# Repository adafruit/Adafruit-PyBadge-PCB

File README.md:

## Adafruit PyBadge PCB

<a href="http://www.adafruit.com/products/4200"><br/>
Click here to purchase one from the Adafruit shop</a>

PCB files for the Adafruit PyBadge. 

Format is EagleCAD schematic and board layout
* https://www.adafruit.com/product/4200

### Description

What's the size of a credit card and can run CircuitPython, MakeCode Arcade or Arduino? That's right, its the **Adafruit PyBadge!** We wanted to see how much we could cram into a ​3 3⁄8 × ​2 1⁄8 inch rounded rectangle, to make an all-in-one dev board with a lot of possibilities, and this is what we came up with.

The PyBadge is a compact board, like we said, it's credit card sized. It's powered by our favorite chip, the ATSAMD51, with 512KB of flash and 192KB of RAM. We add 2 MB of QSPI flash for file storage, handy for images, fonts, sounds, or game assets.

On the front you get a 1.8" 160x128 color TFT display with dimmable backlight - we have fast DMA support for drawing so updates are incredibly fast. There's also 8 silicone-top buttons, they are clicky but have a soft button top so they're nice and grippy. The buttons are arranged to mimic a gaming handheld, with a d-pad, 2 menu-select buttons and 2 fire-action buttons. There's also 5 NeoPixel LEDs to dazzle or track activity.

On the back we have a full Feather-compatible header socket set, so you can plug in any FeatherWing to expand the capabilities of the PyBadge. There's also 3 STEMMA connectors - two 3-pin with ADC/PWM capability and one 4-pin that connects to I2C - you can use this for Grove sensors as well.

For built in sensors, there's a light sensor that points out the front, and a 3-axis accelerometer that can detect taps and free-fall. To make bleeps and bloops, there's a built in buzzer-speaker. [For projects where you need more volume, you can plug in one of our 8 ohm speakers](https://www.adafruit.com/product/3923).

[You can power the PyBadge from any of our LiPoly batteries, but we like this 400mAh one](https://www.adafruit.com/product/3898.) An on-off switch will save battery power when not in use. Or power from the Micro USB port - it will also charge up the battery if one is attached.

Now, how to program it? Well you've got a lot of options!

[MakeCode Arcade is the easiest to start for making games](https://arcade.makecode.com/), you can drag-and-drop blocks and load games over the disk-drive bootloader
[CircuitPython](https://circuitpython.org/board/pybadge/) lets you draw graphics, play wave files and print out text in any fonts - all in Python! There's tons of sensor support as well.
Arduino is low level, powerful, but a little more challenging. [You can use Adafruit Arcada](https://github.com/adafruit/Adafruit_Arcada) to interface with the hardware and it will abstract some of the nitty-gritty details like reading buttons for you.
Here's a list of everything you get

 * **ATSAMD51J19** @ 120MHz with 3.3V logic/power - 512KB of FLASH + 192KB of RAM
 * **2 MB of SPI Flash** for storing images, sounds, animations, whatever!
 * **1.8" 160x128 Color TFT Display** connected to its own SPI port
 * **8 x Game/Control Buttons** with nice silicone button tops (these feel great)
 * **5 x NeoPixels** for badge dazzle, or game score-keeping
 * **Triple-axis accelerometer** (motion sensor)
 * **Light sensor**, reverse-mount so that it points out the front
 * **Built in buzzer mini-speaker**
 * **Mono Class-D speaker driver for** 4-8 ohm speakers, up to 2 Watts
 * LiPoly battery port with built in recharging capability
 * USB port for battery charging, programming and debugging
 * Two female header strips with Feather-compatible pinout so you can plug any FeatherWings in
 * JST ports for NeoPixels, sensor input, and I2C (you can fit I2C Grove connectors in here)
 * Reset button
 * On-Off switch

### License

Adafruit invests time and resources providing this open source design, please support Adafruit and open-source hardware by purchasing products from [Adafruit](https://www.adafruit.com)!

Designed by Limor Fried/Ladyada for Adafruit Industries.

Creative Commons Attribution/Share-Alike, all text above must be included in any redistribution. 
See license.txt for additional details.

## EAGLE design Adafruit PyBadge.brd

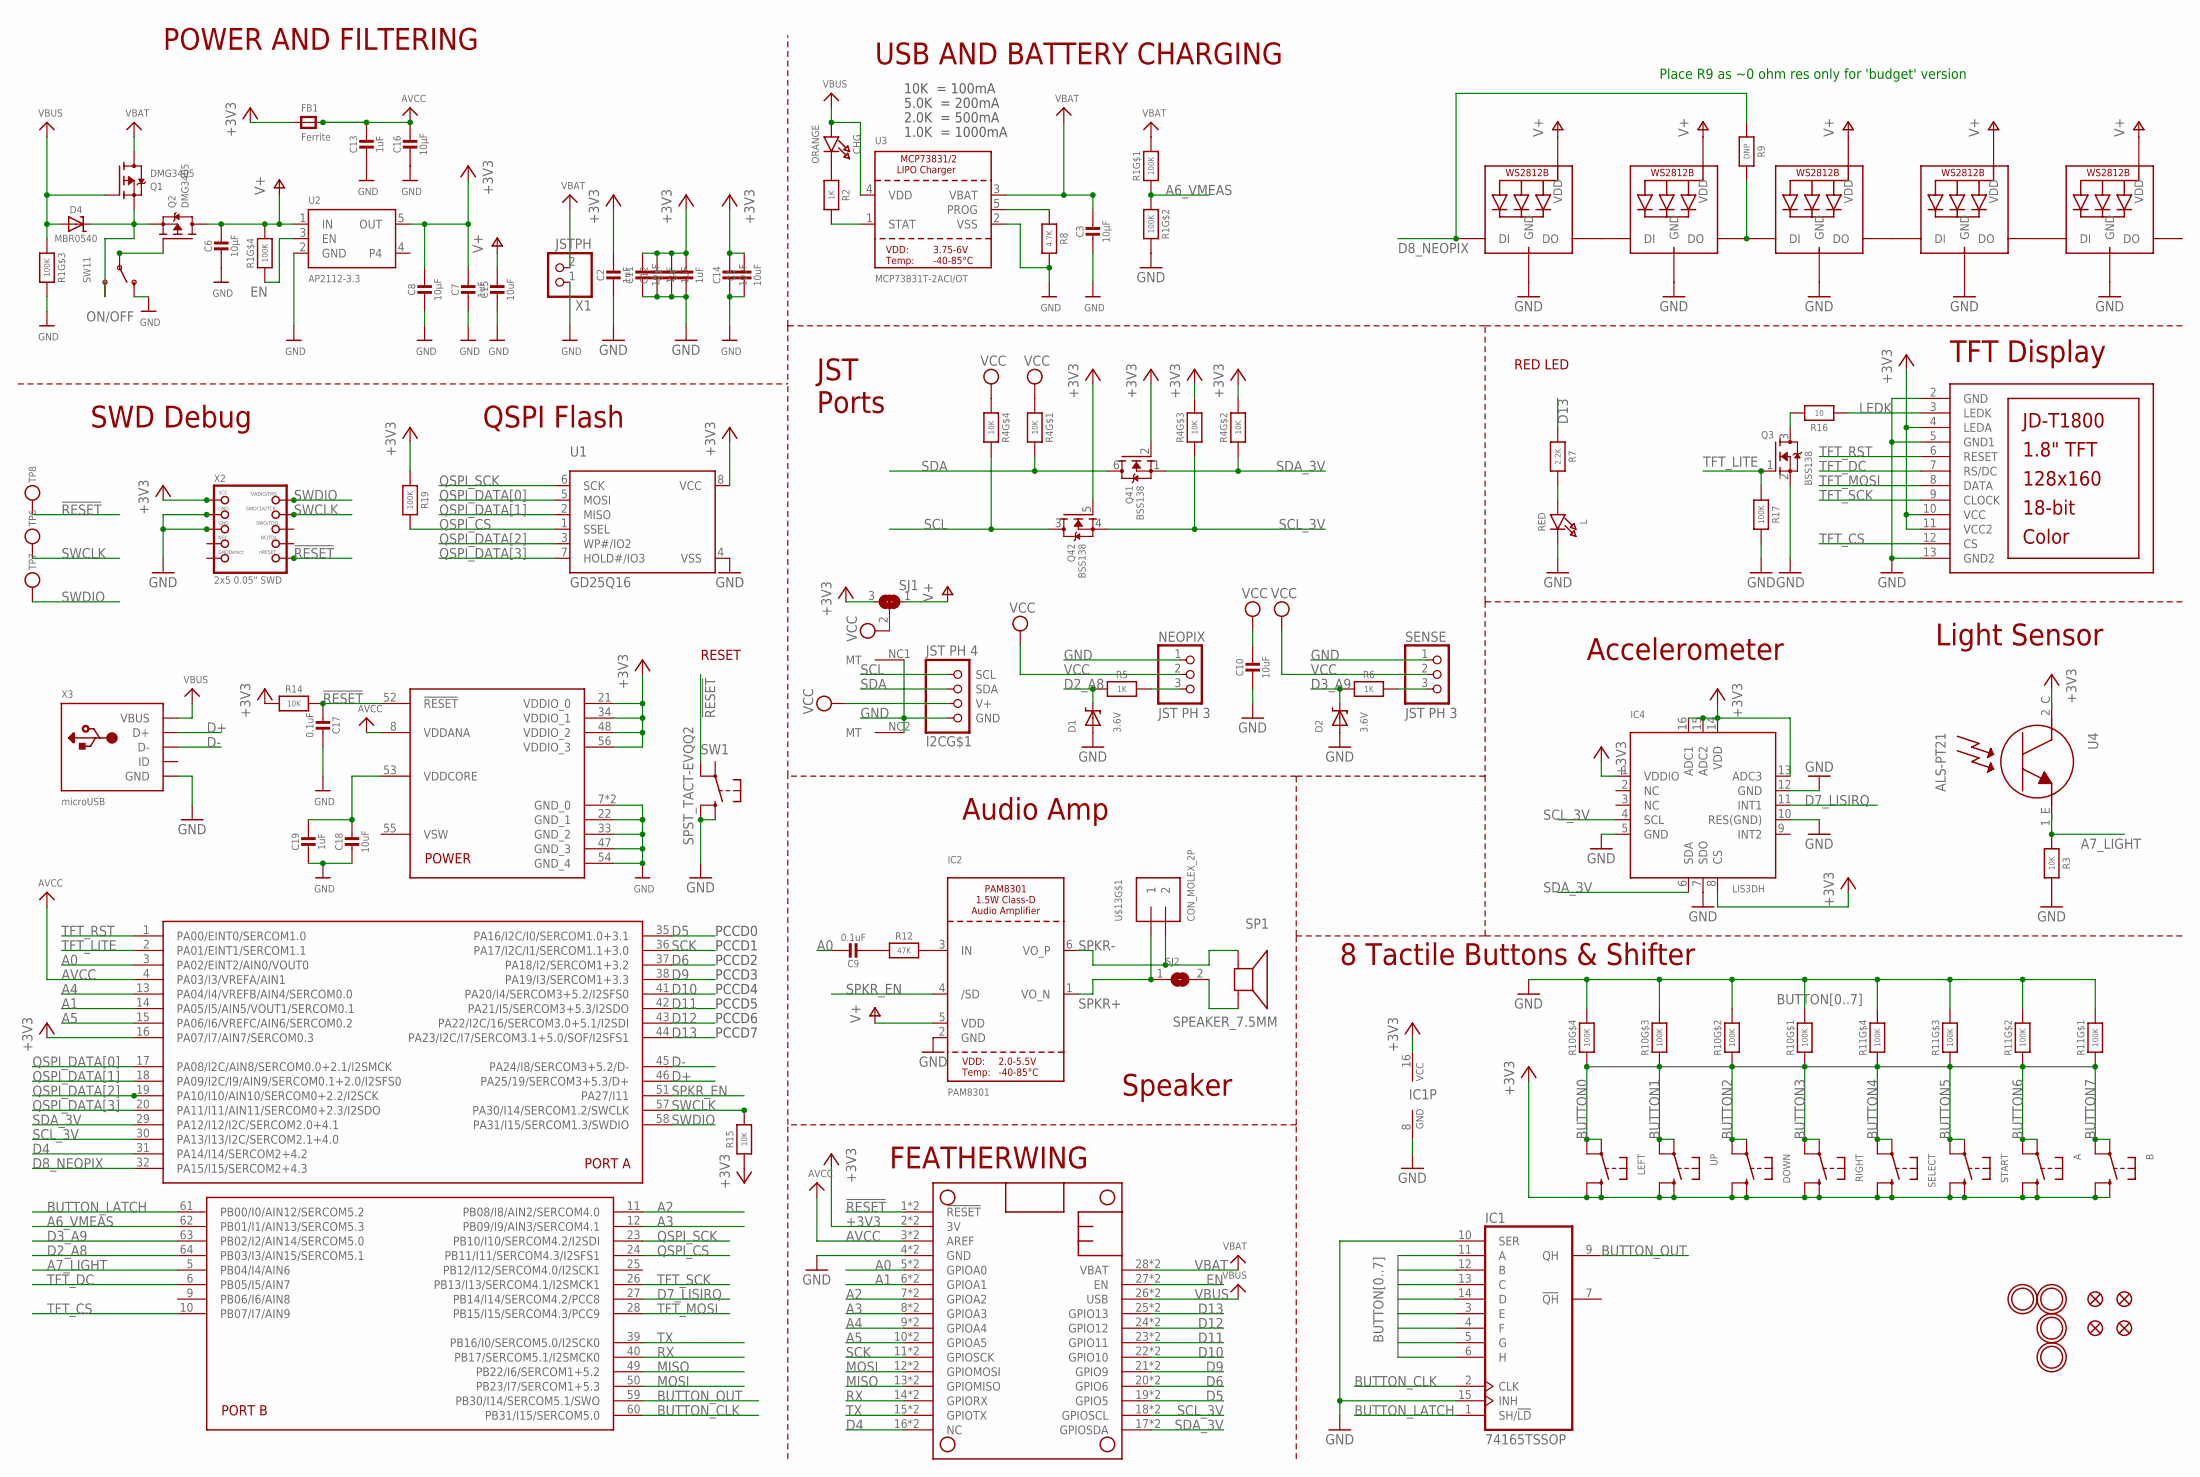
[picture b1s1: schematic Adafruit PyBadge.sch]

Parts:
A: SWITCH_TACT_SMT_6MMSMALL; 6MM_SMT
B: SWITCH_TACT_SMT_6MMSMALL; 6MM_SMT
C1, C2, C4, C7, C12, C13, C19: 1uF; 0603-NO
C3, C6, C8: 10µF; 0805-NO
C5, C10, C11, C14, C15, C18: 10uF; 0805-NO
C9, C17: 0.1uF; 0603-NO
C16: 10µF; _0805MP
CHG: ORANGE; CHIPLED_0805_NOOUTLINE
D1, D2: 3.6V; SOD-323
D4: MBR0540; SOD-123
DOWN: SWITCH_TACT_SMT_6MMSMALL; 6MM_SMT
FB1: Ferrite; 0805-NO
I2C: JST PH 4; JSTPH4
IC1: 74165TSSOP; TSSOP16
IC2: PAM8301; SOT23-6
IC4: LIS3DH; LGA16_3X3MM
L: RED; CHIPLED_0805_NOOUTLINE
LCD1: DISP_LCD_JDT1800; JD-T1800
LED1, LED2, LED3, LED4, LED5: WS2812B3535; LED3535
LEFT: SWITCH_TACT_SMT_6MMSMALL; 6MM_SMT
MS1: FEATHERWING_SMTDUALNOHOLES; FEATHERWING_SMT_NOHOLES
NEOPIX: JST PH 3; JSTPH3
Q1, Q2: DMG3405; SOT23-R
Q3: BSS138; SOT23-WIDE
Q4: BSS138; SOT363
R1, R10, R11: 100K; RESPACK_4X0603
R2, R5, R6: 1K; 0603-NO
R3, R14, R15: 10K; 0603-NO
R4: 10K; RESPACK_4X0603
R7: 2.2K; 0603-NO
R8: 4.7K; 0603-NO
R9: DNP; 0603-NO
R12: 47K; 0603-NO
R16: 10; 0603-NO
R17, R19: 100K; 0603-NO
RIGHT: SWITCH_TACT_SMT_6MMSMALL; 6MM_SMT
SELECT: SWITCH_TACT_SMT_6MMSMALL; 6MM_SMT
SENSE: JST PH 3; JSTPH3
SJ1: SOLDERJUMPER_2WAY; SOLDERJUMPER_2WAY_OPEN_NOPASTE
SJ2: SOLDERJUMPERCLOSED; SOLDERJUMPER_CLOSEDWIRE
SP1: SPEAKER_7.5MM; BUZZER_SMT_7.5MM
START: SWITCH_TACT_SMT_6MMSMALL; 6MM_SMT
SW1: SPST_TACT-EVQQ2; EVQ-Q2_SMALLER
SW11: SWITCH_SPDT; SPDT_SMT_SSSS811101
TP6, TP7, TP8: TESTPOINTROUND2MM; TESTPOINT_ROUND_2MM
U1: GD25Q16; SOIC8_208MIL
U2: AP2112-3.3; SOT23-5
U3: MCP73831T-2ACI/OT; SOT23-5
U4: ALS-PT21; ALS-PT26-21C
U$5, U$6, U$15, U$17: MOUNTINGHOLE3.0THIN; MOUNTINGHOLE_3.0_PLATEDTHIN
U$13: CON_MOLEX_2P; 53398-0271
U$24: ATSAMD51J19; PQFN64-1
U$34, U$35, U$42, U$43: FIDUCIAL_1MM
UP: SWITCH_TACT_SMT_6MMSMALL; 6MM_SMT
X1: JSTPH; JSTPH2
X2: 2x5 0.05" SWD; 2X05_1.27MM_BOX_POSTS
X3: microUSB; 4UCONN_20329_V2

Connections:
!RESET: C17.2, MS1.1 (!RESET), MS1.1B (!RESET), R14.2, SW1.A' (P1), TP8.P$1, U$24.52 (!RESET), X2.10 (NRESET)
+3V3: A.B (S), A.B' (S1), B.B (S), B.B' (S1), C1.1, C2.1, C4.1, C5.1, C7.1, C8.1, C11.1, C12.1, C14.1, DOWN.B (S), DOWN.B' (S1), FB1.1, IC1.16 (VCC), IC4.1 (VDDIO), IC4.8 (CS), IC4.13 (ADC3), IC4.14 (VDD), IC4.15 (ADC2), IC4.16 (ADC1), LCD1.4 (LEDA), LCD1.10 (VCC), LCD1.11 (VCC2), LEFT.B (S), LEFT.B' (S1), MS1.2 (3V), MS1.2B (3V), Q4.2 (G), Q4.5 (G), R4.2 (1), R4.3 (1), R14.1, R15.1, R19.1, RIGHT.B (S), RIGHT.B' (S1), SELECT.B (S), SELECT.B' (S1), SJ1.3, START.B (S), START.B' (S1), U1.8 (VCC), U2.5 (OUT), U4.2_C (C), U$24.16 (PA07/I7/AIN7/SERCOM0.3), U$24.21 (VDDIO_0), U$24.34 (VDDIO_1), U$24.48 (VDDIO_2), U$24.56 (VDDIO_3), UP.B (S), UP.B' (S1), X2.1 (VCC)
A0: C9.1, MS1.5 (GPIOA0), MS1.5B (GPIOA0), U$24.3 (PA02/EINT2/AIN0/VOUT0)
A1: MS1.6 (GPIOA1), MS1.6B (GPIOA1), U$24.14 (PA05/I5/AIN5/VOUT1/SERCOM0.1)
A2: MS1.7 (GPIOA2), MS1.7B (GPIOA2), U$24.11 (PB08/I8/AIN2/SERCOM4.0)
A3: MS1.8 (GPIOA3), MS1.8B (GPIOA3), U$24.12 (PB09/I9/AIN3/SERCOM4.1)
A4: MS1.9 (GPIOA4), MS1.9B (GPIOA4), U$24.13 (PA04/I4/VREFB/AIN4/SERCOM0.0)
A5: MS1.10 (GPIOA5), MS1.10B (GPIOA5), U$24.15 (PA06/I6/VREFC/AIN6/SERCOM0.2)
A6_VMEAS: R1.1, R1.2 (1), U$24.62 (PB01/I1/AIN13/SERCOM5.3)
A7_LIGHT: R3.2, U4.1_E (E), U$24.5 (PB04/I4/AIN6)
AVCC: C13.1, C16.1, FB1.2, MS1.3 (AREF), MS1.3B (AREF), U$24.4 (PA03/I3/VREFA/AIN1), U$24.8 (VDDANA)
BUTTON0: IC1.11 (A), LEFT.A, LEFT.A' (P1), R10.4 (1)
BUTTON1: IC1.12 (B), R10.3 (1), UP.A, UP.A' (P1)
BUTTON2: DOWN.A, DOWN.A' (P1), IC1.13 (C), R10.2 (1)
BUTTON3: IC1.14 (D), R10.1, RIGHT.A, RIGHT.A' (P1)
BUTTON4: IC1.3 (E), R11.4 (1), SELECT.A, SELECT.A' (P1)
BUTTON5: IC1.4 (F), R11.3 (1), START.A, START.A' (P1)
BUTTON6: A.A, A.A' (P1), IC1.5 (G), R11.2 (1)
BUTTON7: B.A, B.A' (P1), IC1.6 (H), R11.1
BUTTON_CLK: IC1.2 (CLK), U$24.60 (PB31/I15/SERCOM5.0)
BUTTON_LATCH: IC1.1 (SH/!LD), U$24.61 (PB00/I0/AIN12/SERCOM5.2)
BUTTON_OUT: IC1.9 (QH), U$24.59 (PB30/I14/SERCOM5.1/SWO)
CHG_LED: R2.2, U3.1 (STAT)
CHG_RATE: R8.1, U3.5 (PROG)
D2_: NEOPIX.3, R5.1
D2_A8: D1.C, R5.2, U$24.64 (PB03/I3/AIN15/SERCOM5.1)
D3_: R6.1, SENSE.3
D3_A9: D2.C, R6.2, U$24.63 (PB02/I2/AIN14/SERCOM5.0)
D4: MS1.16 (NC), MS1.16B (NC), U$24.31 (PA14/I14/SERCOM2+4.2)
D5: MS1.19 (GPIO5), MS1.19B (GPIO5), U$24.35 (PA16/I2C/I0/SERCOM1.0+3.1)
D6: MS1.20 (GPIO6), MS1.20B (GPIO6), U$24.37 (PA18/I2/SERCOM1+3.2)
D7_LISIRQ: IC4.11 (INT1), U$24.27 (PB14/I14/SERCOM4.2/PCC8)
D8_NEOPIX: LED1.1 (DI), R9.1, U$24.32 (PA15/I15/SERCOM2+4.3)
D9: MS1.21 (GPIO9), MS1.21B (GPIO9), U$24.38 (PA19/I3/SERCOM1+3.3)
D10: MS1.22 (GPIO10), MS1.22B (GPIO10), U$24.41 (PA20/I4/SERCOM3+5.2/I2SFS0)
D11: MS1.23 (GPIO11), MS1.23B (GPIO11), U$24.42 (PA21/I5/SERCOM3+5.3/I2SDO)
D12: MS1.24 (GPIO12), MS1.24B (GPIO12), U$24.43 (PA22/I2C/16/SERCOM3.0+5.1/I2SDI)
D13: MS1.25 (GPIO13), MS1.25B (GPIO13), R7.1, U$24.44 (PA23/I2C/I7/SERCOM3.1+5.0/SOF/I2SFS1)
D+: U$24.46 (PA25/19/SERCOM3+5.3/D+), X3.D+
D-: U$24.45 (PA24/I8/SERCOM3+5.2/D-), X3.D-
EN: MS1.27 (EN), MS1.27B (EN), R1.4 (1), U2.3 (EN)
GND: C1.2, C2.2, C3.2, C4.2, C5.2, C6.2, C7.2, C8.2, C10.2, C11.2, C12.2, C13.2, C14.2, C15.2, C16.2, C17.1, C18.2, C19.2, D1.A, D2.A, I2C.1 (GND), I2C.NC1 (MT), I2C.NC2 (MT), IC1.8 (GND), IC1.10 (SER), IC1.15 (INH), IC2.2 (GND), IC4.5 (GND), IC4.7 (SDO), IC4.10 (RES(GND)), IC4.12 (GND), L.C, LCD1.2 (GND), LCD1.5 (GND1), LCD1.13 (GND2), LED1.4 (GND), LED2.4 (GND), LED3.4 (GND), LED4.4 (GND), LED5.4 (GND), MS1.4 (GND), MS1.4B (GND), NEOPIX.1, Q3.2 (S), R1.6 (2), R1.7 (2), R3.1, R8.2, R10.5 (2), R10.6 (2), R10.7 (2), R10.8 (2), R11.5 (2), R11.6 (2), R11.7 (2), R11.8 (2), R17.2, SENSE.1, SW1.B (S), SW1.B' (S1), SW11.A (O), U1.4 (VSS), U2.2 (GND), U3.2 (VSS), U$24.7 (GND_0), U$24.22 (GND_1), U$24.33 (GND_2), U$24.47 (GND_3), U$24.54 (GND_4), U$24.EXP (GND_0), X1.1, X2.3 (GND), X2.5 (GND), X3.BASE@1 (GND), X3.BASE@2 (GND), X3.GND, X3.SPRT@1 (GND), X3.SPRT@2 (GND), X3.SPRT@3 (GND), X3.SPRT@4 (GND)
LEDK: LCD1.3 (LEDK), R16.1
MISO: MS1.13 (GPIOMISO), MS1.13B (GPIOMISO), U$24.49 (PB22/I6/SERCOM1+5.2)
MOSI: MS1.12 (GPIOMOSI), MS1.12B (GPIOMOSI), U$24.50 (PB23/I7/SERCOM1+5.3)
unnamed: CHG.C, R2.1
unnamed: L.A, R7.2
unnamed: LED1.3 (DO), LED2.1 (DI)
unnamed: LED2.3 (DO), LED3.1 (DI), R9.2
unnamed: LED3.3 (DO), LED4.1 (DI)
unnamed: Q3.3 (D), R16.2
unnamed: LED4.3 (DO), LED5.1 (DI)
unnamed: D4.C, Q1.2 (S), Q2.2 (S), SW11.C (S)
unnamed: C9.2, R12.1
unnamed: IC2.3 (IN), R12.2
unnamed: SJ2.2, SP1.-
ON/OFF: Q2.1 (G), SW11.B
QSPI_CS: R19.2, U1.1 (SSEL), U$24.24 (PB11/I11/SERCOM4.3/I2SFS1)
QSPI_DATA[0]: U1.5 (MOSI), U$24.17 (PA08/I2C/AIN8/SERCOM0.0+2.1/I2SMCK)
QSPI_DATA[1]: U1.2 (MISO), U$24.18 (PA09/I2C/I9/AIN9/SERCOM0.1+2.0/I2SFS0)
QSPI_DATA[2]: U1.3 (WP#/IO2), U$24.19 (PA10/I10/AIN10/SERCOM0+2.2/I2SCK)
QSPI_DATA[3]: U1.7 (HOLD#/IO3), U$24.20 (PA11/I11/AIN11/SERCOM0+2.3/I2SDO)
QSPI_SCK: U1.6 (SCK), U$24.23 (PB10/I10/SERCOM4.2/I2SDI)
RX: MS1.14 (GPIORX), MS1.14B (GPIORX), U$24.40 (PB17/SERCOM5.1/I2SMCK0)
SCK: MS1.11 (GPIOSCK), MS1.11B (GPIOSCK), U$24.36 (PA17/I2C/I1/SERCOM1.1+3.0)
SCL: I2C.4 (SCL), Q4.3 (D), R4.5 (2)
SCL_3V: IC4.4 (SCL), MS1.18 (GPIOSCL), MS1.18B (GPIOSCL), Q4.4 (S), R4.6 (2), U$24.30 (PA13/I13/I2C/SERCOM2.1+4.0)
SDA: I2C.3 (SDA), Q4.6 (D), R4.8 (2)
SDA_3V: IC4.6 (SDA), MS1.17 (GPIOSDA), MS1.17B (GPIOSDA), Q4.1 (S), R4.7 (2), U$24.29 (PA12/I12/I2C/SERCOM2.0+4.1)
SPKR+: IC2.1 (VO_N), SJ2.1, U$13.1
SPKR-: IC2.6 (VO_P), SP1.+, U$13.2
SPKR_EN: IC2.4 (/SD), U$24.51 (PA27/I11)
SWCLK: R15.2, TP6.P$1, U$24.57 (PA30/I14/SERCOM1.2/SWCLK), X2.4 (SWDCLK)
SWDIO: TP7.P$1, U$24.58 (PA31/I15/SERCOM1.3/SWDIO), X2.2 (SWDIO)
TFT_CS: LCD1.12 (CS), U$24.10 (PB07/I7/AIN9)
TFT_DC: LCD1.7 (RS/DC), U$24.6 (PB05/I5/AIN7)
TFT_LITE: Q3.1 (G), R17.1, U$24.2 (PA01/EINT1/SERCOM1.1)
TFT_MOSI: LCD1.8 (DATA), U$24.28 (PB15/I15/SERCOM4.3/PCC9)
TFT_RST: LCD1.6 (RESET), U$24.1 (PA00/EINT0/SERCOM1.0)
TFT_SCK: LCD1.9 (CLOCK), U$24.26 (PB13/I13/SERCOM4.1/I2SMCK1)
TX: MS1.15 (GPIOTX), MS1.15B (GPIOTX), U$24.39 (PB16/I0/SERCOM5.0/I2SCK0)
V+: C6.1, C15.1, IC2.5 (VDD), LED1.2 (VDD), LED2.2 (VDD), LED3.2 (VDD), LED4.2 (VDD), LED5.2 (VDD), Q2.3 (D), R1.5 (2), SJ1.1, U2.1 (IN)
VBAT: C3.1, MS1.28 (VBAT), MS1.28B (VBAT), Q1.3 (D), R1.8 (2), U3.3 (VBAT), X1.2
VBUS: CHG.A, D4.A, MS1.26 (USB), MS1.26B (USB), Q1.1 (G), R1.3 (1), U3.4 (VDD), X3.VBUS
VCC: C10.1, I2C.2 (V+), NEOPIX.2, R4.1, R4.4 (1), SENSE.2, SJ1.2
VDDCORE2: C18.1, C19.1, U$24.53 (VDDCORE)

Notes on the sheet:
POWER AND FILTERING
RESET
10K = 100mA
5.0K = 200mA
2.0K = 500mA
1.0K = 1000mA
USB AND BATTERY CHARGING
RED LED
Accelerometer
Light Sensor
FEATHERWING
TFT Display
Audio Amp
JST Ports
PCCD0
PCCD1
PCCD2
PCCD3
PCCD4
PCCD5
PCCD6
PCCD7
Speaker
Place R9 as ~0 ohm res only for 'budget' version
8 Tactile Buttons & Shifter
SWD Debug
QSPI Flash

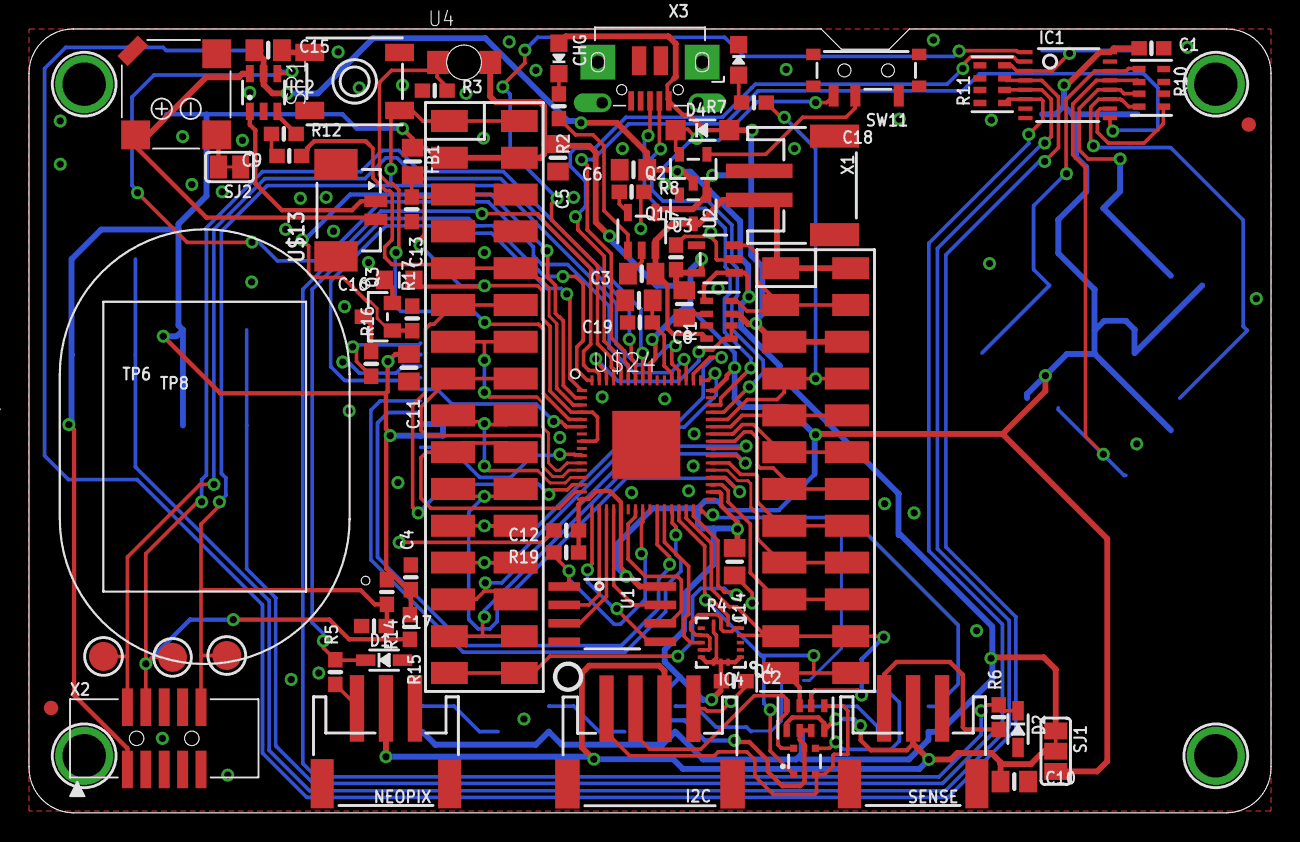
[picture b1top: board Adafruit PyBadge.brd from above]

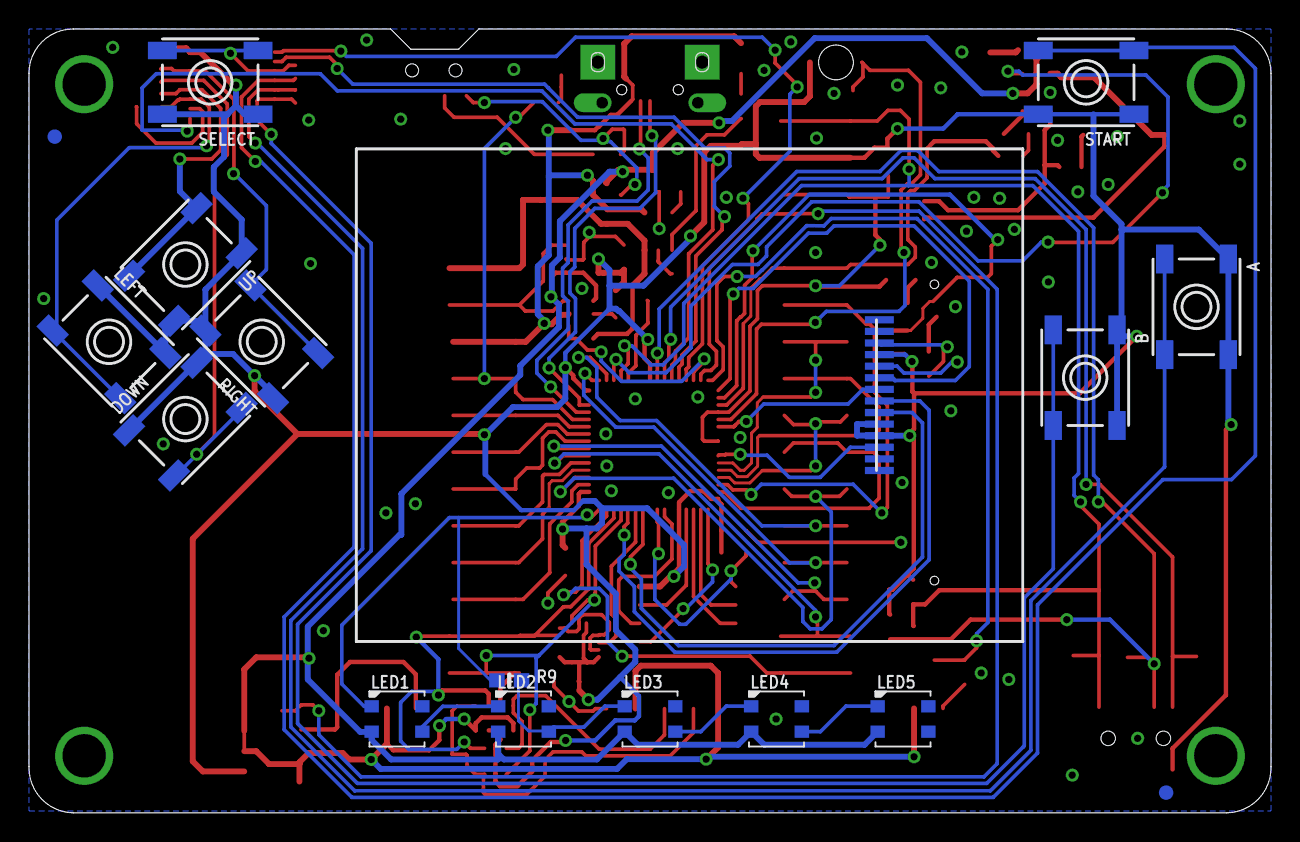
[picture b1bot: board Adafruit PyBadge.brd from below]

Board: 2 copper layers, 85.7 x 54.1 mm, 96 parts (18 on the bottom side), 86 nets.

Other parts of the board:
U$8: SPEAKER_OVAL8OHM
U$18: PYBADGE_TOP
U$32: PYBADGE_BOT
U$37: PCBFEAT-REV-040

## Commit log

2019-04-29 Adding PCB files
2019-07-17 updated to use cookiecutter for pcb repos
2019-07-24 fix typo

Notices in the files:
parts and their libraries:
microbuilder: This work is placed in the public domain, and may be freely used for commercial and non-commercial work with the following conditions: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
